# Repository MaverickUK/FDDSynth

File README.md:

# HDD Synth
<div style="background: white; display: inline-block; padding: 8px;">
  
</div>

### Recreates the sound of mechanical spinning FDDs on retro PCs that use a solid state floppy drive.

The first project I created was the [HDD Synth](https://github.com/MaverickUK/HDDSynth) and so bringing the sound back to floppy disk drives felt like the next logical step.

The FDD Synth listens to the signals on the FDD cable that indicate when the motor is spinning and when the head is moving. It essentially recreates those physical actions in software, meaning that when the FDD motor starts spinning the disk it'll play a short spinup sound before a looping spin sound continues. FDD head movement is monitored and replicated with a short click for small movement along with hum of move rapid track changes. 

## Features

- **Plug and Play**: Uses FDD cable to monitor the exact FDD activity, so all you have to do it plug it in
- **SD Card Storage**: Audio samples stored on removable SD card for easy customization
- **Configurable**: Future software based enhancements planned

## Progress
### 🔄  Phase 1: Breadboard prototype
### 🔄 Phase 2: PCB prototype
### 🌱 Phase 3: PCB final 

<!-- ## Media
[View gallery](media.md) -->

## Contact
Peter Bridger at [maverickuk@gmail.com](maverickuk@gmail.com)

<!--
## Resources

## Acknowledgments
-->

## License
This project is licensed under the GNU General Public License v3.0.

- **Permissions:** Commercial use, modification, and distribution are allowed.
- **Conditions:** You must include a copy of the license and the source code for any derivative works.
- **Prohibitions:** You cannot close the source or use a different license for derivative works.

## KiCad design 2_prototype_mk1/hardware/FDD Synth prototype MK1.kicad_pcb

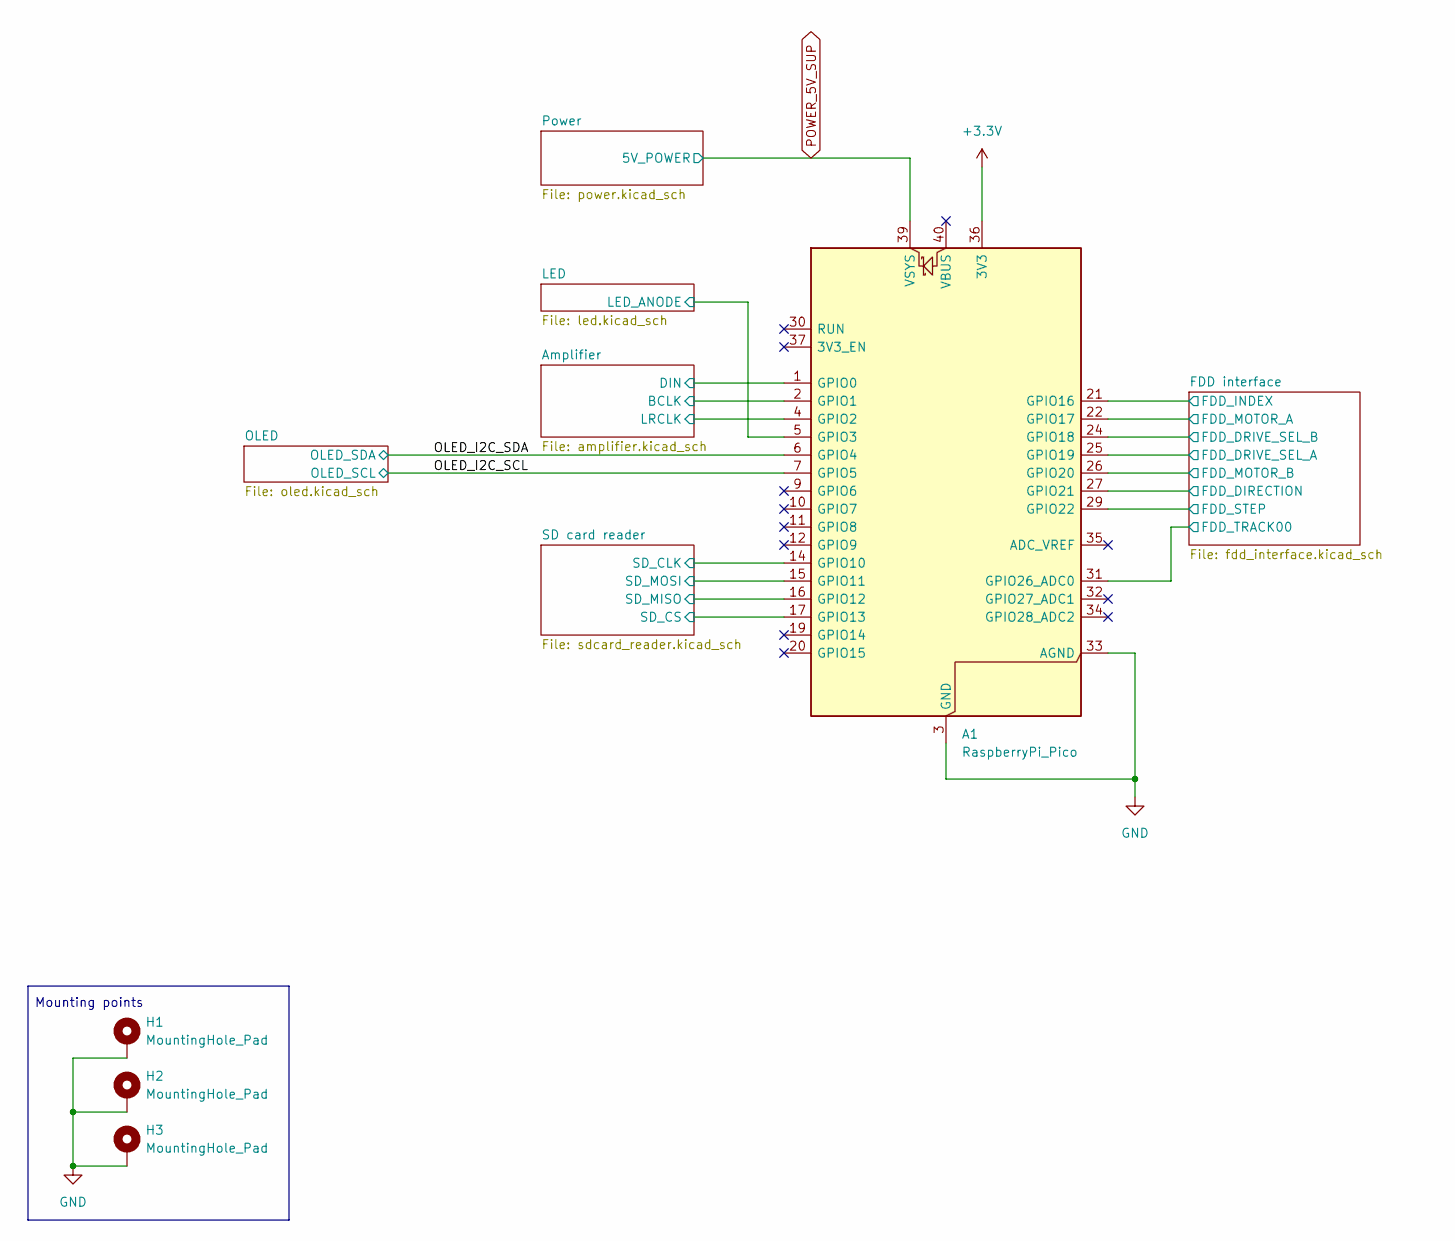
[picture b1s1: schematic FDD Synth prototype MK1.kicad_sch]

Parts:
A1: RaspberryPi_Pico; RaspberryPi_Pico_Common_Unspecified
H1, H2, H3: MountingHole_Pad; MountingHole_3.2mm_M3_Pad_Via

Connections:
+3.3V: A1.36 (3V3); also elsewhere on the board
/Amplifier/BCLK: A1.2 (GPIO1); also elsewhere on the board
/Amplifier/DIN: A1.1 (GPIO0); also elsewhere on the board
/Amplifier/LRCLK: A1.4 (GPIO2); also elsewhere on the board
/FDD interface/FDD_DIRECTION: A1.27 (GPIO21); also elsewhere on the board
/FDD interface/FDD_DRIVE_SEL_A: A1.25 (GPIO19); also elsewhere on the board
/FDD interface/FDD_DRIVE_SEL_B: A1.24 (GPIO18); also elsewhere on the board
/FDD interface/FDD_INDEX: A1.21 (GPIO16); also elsewhere on the board
/FDD interface/FDD_MOTOR_A: A1.22 (GPIO17); also elsewhere on the board
/FDD interface/FDD_MOTOR_B: A1.26 (GPIO20); also elsewhere on the board
/FDD interface/FDD_STEP: A1.29 (GPIO22); also elsewhere on the board
/FDD interface/FDD_TRACK00: A1.31 (GPIO26_ADC0); also elsewhere on the board
/LED/LED_ANODE: A1.5 (GPIO3); also elsewhere on the board
/OLED_I2C_SCL: A1.7 (GPIO5); also elsewhere on the board
/OLED_I2C_SDA: A1.6 (GPIO4); also elsewhere on the board
/SD card reader/SD_CLK: A1.14 (GPIO10); also elsewhere on the board
/SD card reader/SD_CS: A1.17 (GPIO13); also elsewhere on the board
/SD card reader/SD_MISO: A1.16 (GPIO12); also elsewhere on the board
/SD card reader/SD_MOSI: A1.15 (GPIO11); also elsewhere on the board
GND: A1.3 (GND), A1.8 (GND), A1.13 (GND), A1.18 (GND), A1.23 (GND), A1.28 (GND), A1.33 (AGND), A1.38 (GND), H1.1 (1_1), H2.1 (1_1), H3.1 (1_1); also elsewhere on the board
POWER_5V_SUP: A1.39 (VSYS); also elsewhere on the board

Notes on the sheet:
Mounting points

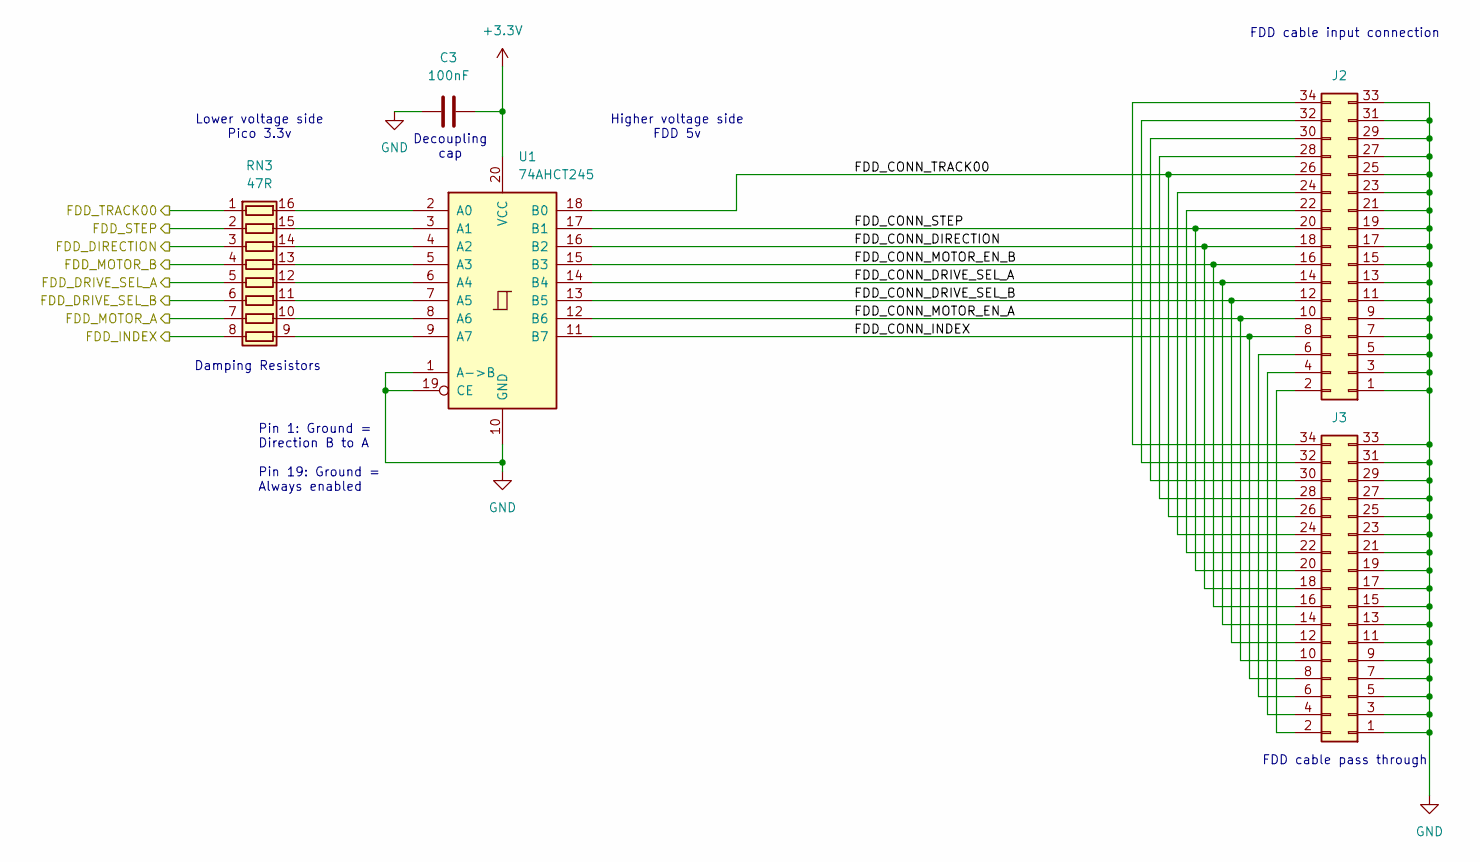
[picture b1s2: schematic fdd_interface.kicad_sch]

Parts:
C3: 100nF; C_0603_1608Metric
J2, J3: Conn_02x17_Odd_Even; IDC-Header_2x17_P2.54mm_Vertical
RN3: 47R; R_Array_Convex_8x0602
U1: 74AHCT245; SOIC-20W_7.5x12.8mm_P1.27mm

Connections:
+3.3V: C3.2, U1.20 (VCC); also elsewhere on the board
/FDD interface/FDD_CONN_DIRECTION: J2.18, J3.18, U1.16 (B2)
/FDD interface/FDD_CONN_DRIVE_SEL_A: J2.14, J3.14, U1.14 (B4)
/FDD interface/FDD_CONN_DRIVE_SEL_B: J2.12, J3.12, U1.13 (B5)
/FDD interface/FDD_CONN_INDEX: J2.8, J3.8, U1.11 (B7)
/FDD interface/FDD_CONN_MOTOR_EN_A: J2.10, J3.10, U1.12 (B6)
/FDD interface/FDD_CONN_MOTOR_EN_B: J2.16, J3.16, U1.15 (B3)
/FDD interface/FDD_CONN_STEP: J2.20, J3.20, U1.17 (B1)
/FDD interface/FDD_CONN_TRACK00: J2.26, J3.26, U1.18 (B0)
/FDD interface/FDD_DIRECTION: RN3.3 (R3.1); also elsewhere on the board
/FDD interface/FDD_DRIVE_SEL_A: RN3.5 (R5.1); also elsewhere on the board
/FDD interface/FDD_DRIVE_SEL_B: RN3.6 (R6.1); also elsewhere on the board
/FDD interface/FDD_INDEX: RN3.8 (R8.1); also elsewhere on the board
/FDD interface/FDD_MOTOR_A: RN3.7 (R7.1); also elsewhere on the board
/FDD interface/FDD_MOTOR_B: RN3.4 (R4.1); also elsewhere on the board
/FDD interface/FDD_STEP: RN3.2 (R2.1); also elsewhere on the board
/FDD interface/FDD_TRACK00: RN3.1 (R1.1); also elsewhere on the board
GND: C3.1, J2.1, J2.3, J2.5, J2.7, J2.9, J2.11, J2.13, J2.15, J2.17, J2.19, J2.21, J2.23, J2.25, J2.27, J2.29, J2.31, J2.33, J3.1, J3.3, J3.5, J3.7, J3.9, J3.11, J3.13, J3.15, J3.17, J3.19, J3.21, J3.23, J3.25, J3.27, J3.29, J3.31, J3.33, U1.1 (A->B), U1.10 (GND), U1.19 (CE); also elsewhere on the board
unnamed: J2.2, J3.2
unnamed: J2.4, J3.4
unnamed: J2.6, J3.6
unnamed: J2.22, J3.22
unnamed: J2.24, J3.24
unnamed: J2.28, J3.28
unnamed: J2.30, J3.30
unnamed: J2.32, J3.32
unnamed: J2.34, J3.34
unnamed: RN3.16 (R1.2), U1.2 (A0)
unnamed: RN3.15 (R2.2), U1.3 (A1)
unnamed: RN3.14 (R3.2), U1.4 (A2)
unnamed: RN3.13 (R4.2), U1.5 (A3)
unnamed: RN3.12 (R5.2), U1.6 (A4)
unnamed: RN3.11 (R6.2), U1.7 (A5)
unnamed: RN3.10 (R7.2), U1.8 (A6)
unnamed: RN3.9 (R8.2), U1.9 (A7)

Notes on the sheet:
Pin 1: Ground = Direction B to A Pin 19: Ground = Always enabled
Decoupling cap
Damping Resistors
Lower voltage side Pico 3.3v
Higher voltage side FDD 5v
FDD cable input connection
FDD cable pass through

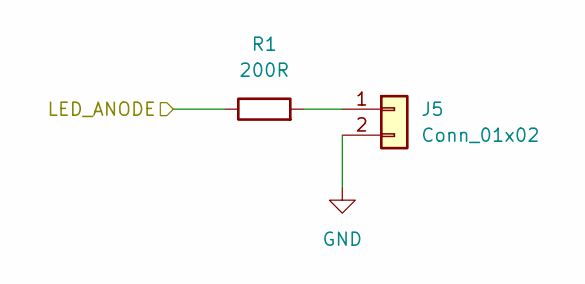
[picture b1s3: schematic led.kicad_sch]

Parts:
J5: Conn_01x02; PinHeader_1x02_P2.54mm_Vertical
R1: 200R; R_0805_2012Metric

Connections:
/LED/LED_ANODE: R1.1; also elsewhere on the board
GND: J5.2; also elsewhere on the board
unnamed: J5.1, R1.2

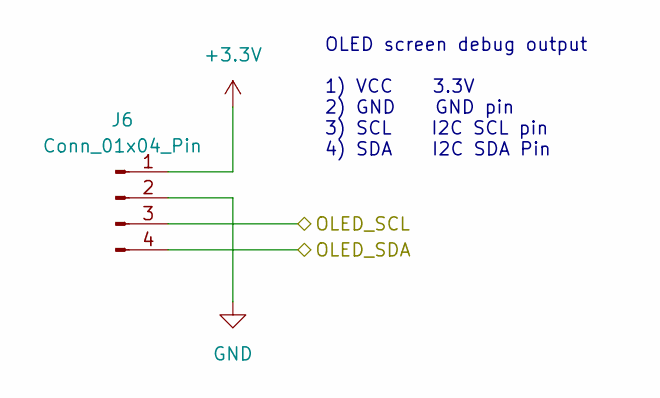
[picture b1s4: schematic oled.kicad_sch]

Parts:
J6: Conn_01x04_Pin; PinSocket_1x04_P2.54mm_Vertical

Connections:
+3.3V: J6.1; also elsewhere on the board
/OLED_I2C_SCL: J6.3; also elsewhere on the board
/OLED_I2C_SDA: J6.4; also elsewhere on the board
GND: J6.2; also elsewhere on the board

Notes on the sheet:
OLED screen debug output 1) VCC 3.3V 2) GND GND pin 3) SCL I2C SCL pin 4) SDA I2C SDA Pin

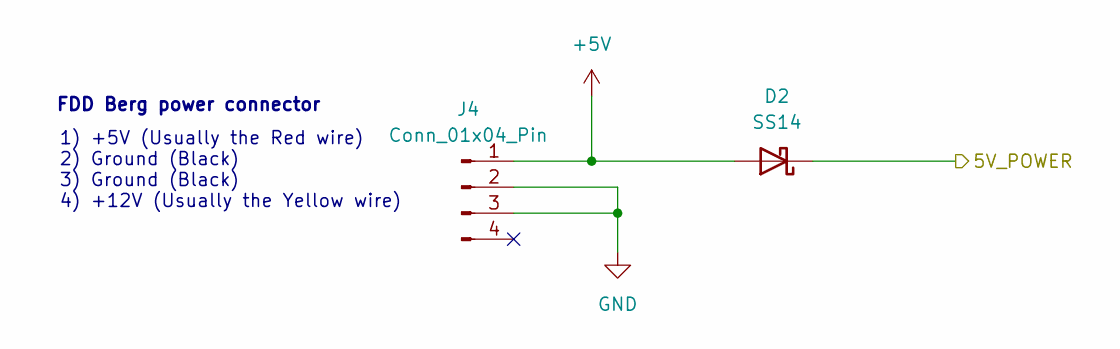
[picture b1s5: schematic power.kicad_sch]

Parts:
D2: SS14; D_SMA
J4: Conn_01x04_Pin; Molex_KK-254_AE-6410-04A_1x04_P2.54mm_Vertical

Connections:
+5V: D2.2 (A), J4.1
GND: J4.2, J4.3; also elsewhere on the board
POWER_5V_SUP: D2.1 (K); also elsewhere on the board

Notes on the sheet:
FDD Berg power connector
1) +5V (Usually the Red wire) 2) Ground (Black) 3) Ground (Black) 4) +12V (Usually the Yellow wire)

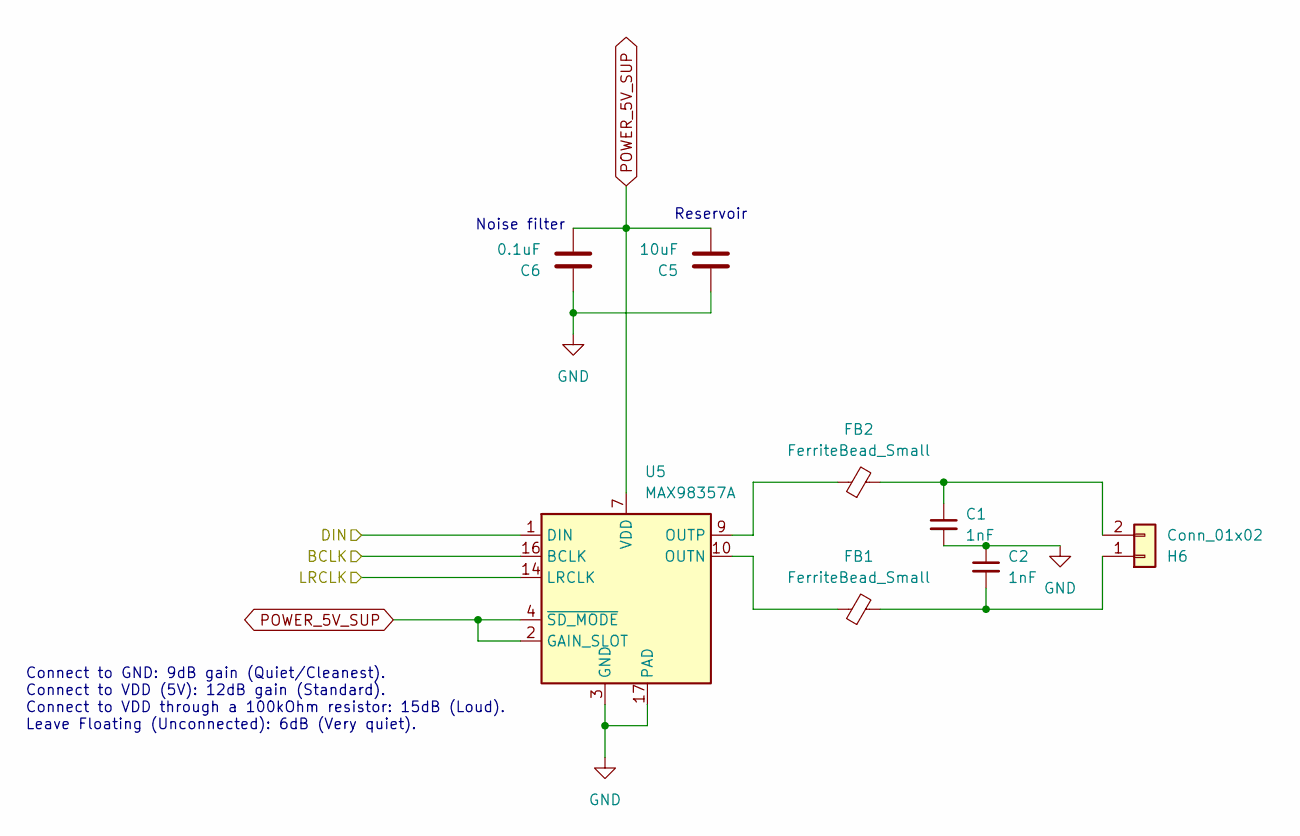
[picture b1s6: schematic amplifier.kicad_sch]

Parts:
C1, C2: 1nF; C_0603_1608Metric; Manufacturer_Part_Number 0603B102K500NT
C5: 10uF; C_1206_3216Metric; Manufacturer_Part_Number CL31A106KAHNNNE
C6: 0.1uF; C_0603_1608Metric; Manufacturer_Part_Number CL10B104KO8NNNC
FB1, FB2: FerriteBead_Small; L_0805_2012Metric; Manufacturer_Part_Number BLM21PG221SN1D; LCSC_Part_Number C85840
H6: Conn_01x02; TerminalBlock_Phoenix_PT-1,5-2-3.5-H_1x02_P3.50mm_Horizontal; Manufacturer_Part_Number 1984617; LCSC_Part_Number C3819527
U5: MAX98357A; TQFN-16-1EP_3x3mm_P0.5mm_EP1.23x1.23mm; Manufacturer_Part_Number MAX98357AETE+T; LCSC_Part_Number C910544

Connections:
/Amplifier/BCLK: U5.16 (BCLK); also elsewhere on the board
/Amplifier/DIN: U5.1 (DIN); also elsewhere on the board
/Amplifier/LRCLK: U5.14 (LRCLK); also elsewhere on the board
GND: C1.2, C2.1, C5.1, C6.1, U5.3 (GND), U5.11 (GND), U5.15 (GND), U5.17 (PAD); also elsewhere on the board
unnamed: C2.2, FB1.2, H6.1
unnamed: C1.1, FB2.2, H6.2
unnamed: FB1.1, U5.10 (OUTN)
unnamed: FB2.1, U5.9 (OUTP)
POWER_5V_SUP: C5.2, C6.2, U5.2 (GAIN_SLOT), U5.4 (~SD_MODE), U5.7 (VDD), U5.8 (VDD); also elsewhere on the board

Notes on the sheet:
Connect to GND: 9dB gain (Quiet/Cleanest). Connect to VDD (5V): 12dB gain (Standard). Connect to VDD through a 100kOhm resistor: 15dB (Loud). Leave Floating (Unconnected): 6dB (Very quiet).
Reservoir
Noise filter

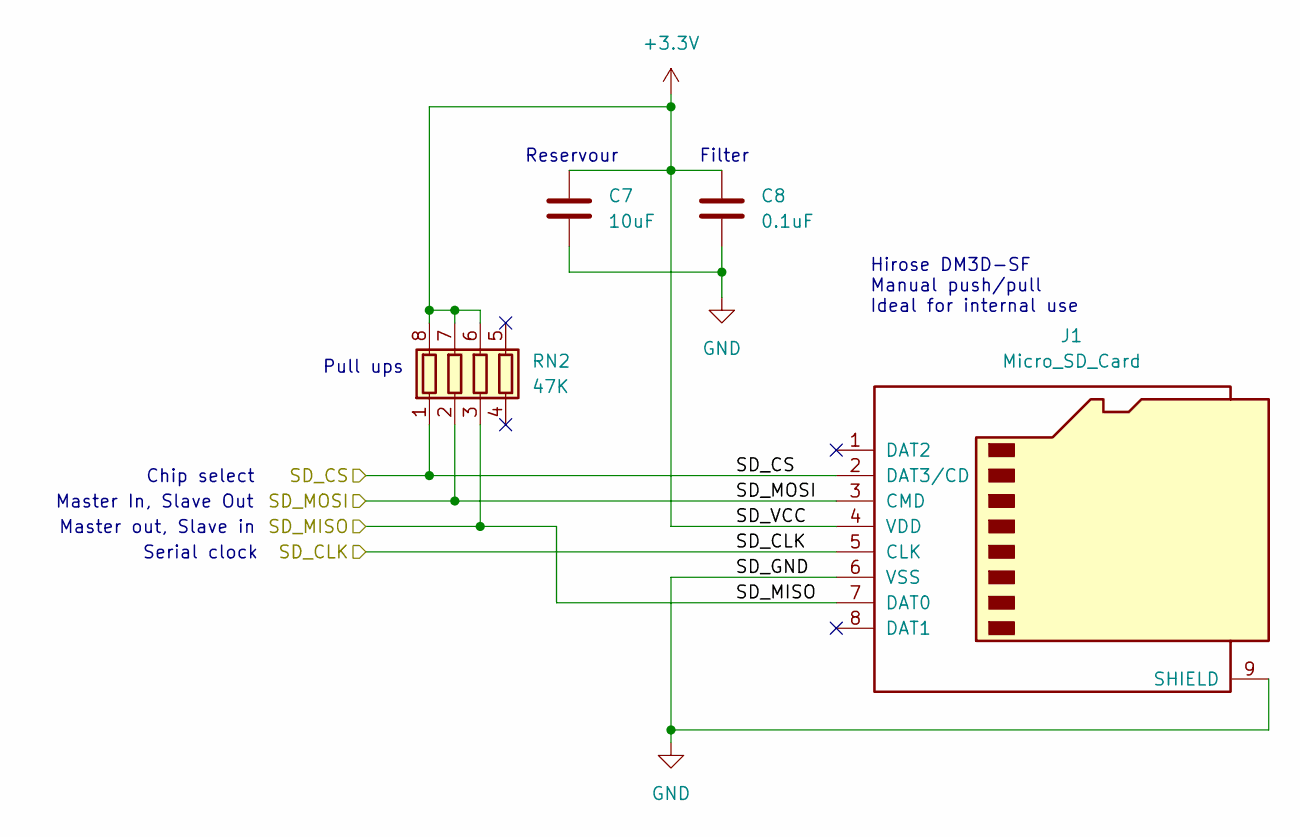
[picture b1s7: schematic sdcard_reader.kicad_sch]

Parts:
C7: 10uF; C_1206_3216Metric; Manufacturer_Part_Number CL31A106KAHNNNE
C8: 0.1uF; C_0603_1608Metric; Manufacturer_Part_Number CL10B104KO8NNNC
J1: Micro_SD_Card; microSD_HC_Hirose_DM3D-SF; Manufacturer_Part_Number DM3D-SF; LCSC_Part_Number C719027
RN2: 47K; R_Array_Convex_4x0603; Manufacturer_Part_Number YC164-JR-0747KL; LCSC_Part_Number C779384

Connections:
+3.3V: C7.1, C8.1, J1.4 (VDD), RN2.6 (R3.2), RN2.7 (R2.2), RN2.8 (R1.2); also elsewhere on the board
/SD card reader/SD_CLK: J1.5 (CLK); also elsewhere on the board
/SD card reader/SD_CS: J1.2 (DAT3/CD), RN2.1 (R1.1); also elsewhere on the board
/SD card reader/SD_MISO: J1.7 (DAT0), RN2.3 (R3.1); also elsewhere on the board
/SD card reader/SD_MOSI: J1.3 (CMD), RN2.2 (R2.1); also elsewhere on the board
GND: C7.2, C8.2, J1.6 (VSS), J1.9 (SHIELD); also elsewhere on the board

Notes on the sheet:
Master In, Slave Out
Pull ups
Filter
Chip select
Master out, Slave in
Reservour
Serial clock
Hirose DM3D-SF Manual push/pull Ideal for internal use

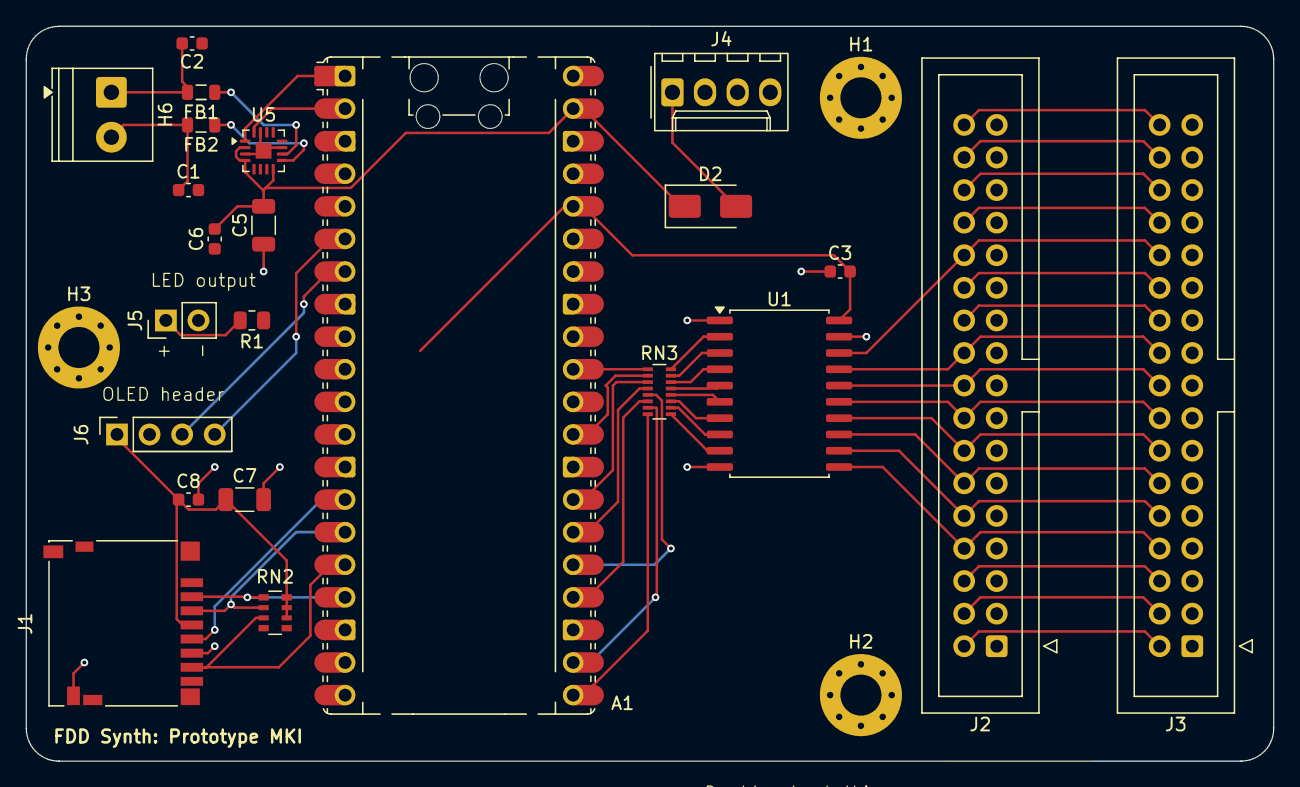
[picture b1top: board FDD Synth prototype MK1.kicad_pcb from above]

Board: 2 copper layers, 97.2 x 57.3 mm, 26 parts (0 on the bottom side), 52 nets.

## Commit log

2026-04-20 Setup initial gitignore
2026-04-20 Create basic starting point of design
2026-04-21 Created basic PCB
2026-04-21 Created README
2026-04-21 Add OLED screen header
2026-04-21 Create LED and OLED connections
2026-04-21 Add PCB renders to README
2026-04-23 Quick and dirty layout of traces - not final
2026-04-24 Switch out SD card reader for correct footprint
2026-04-28 Split power into own schematic
2026-04-28 Change power connector and reroute amp
